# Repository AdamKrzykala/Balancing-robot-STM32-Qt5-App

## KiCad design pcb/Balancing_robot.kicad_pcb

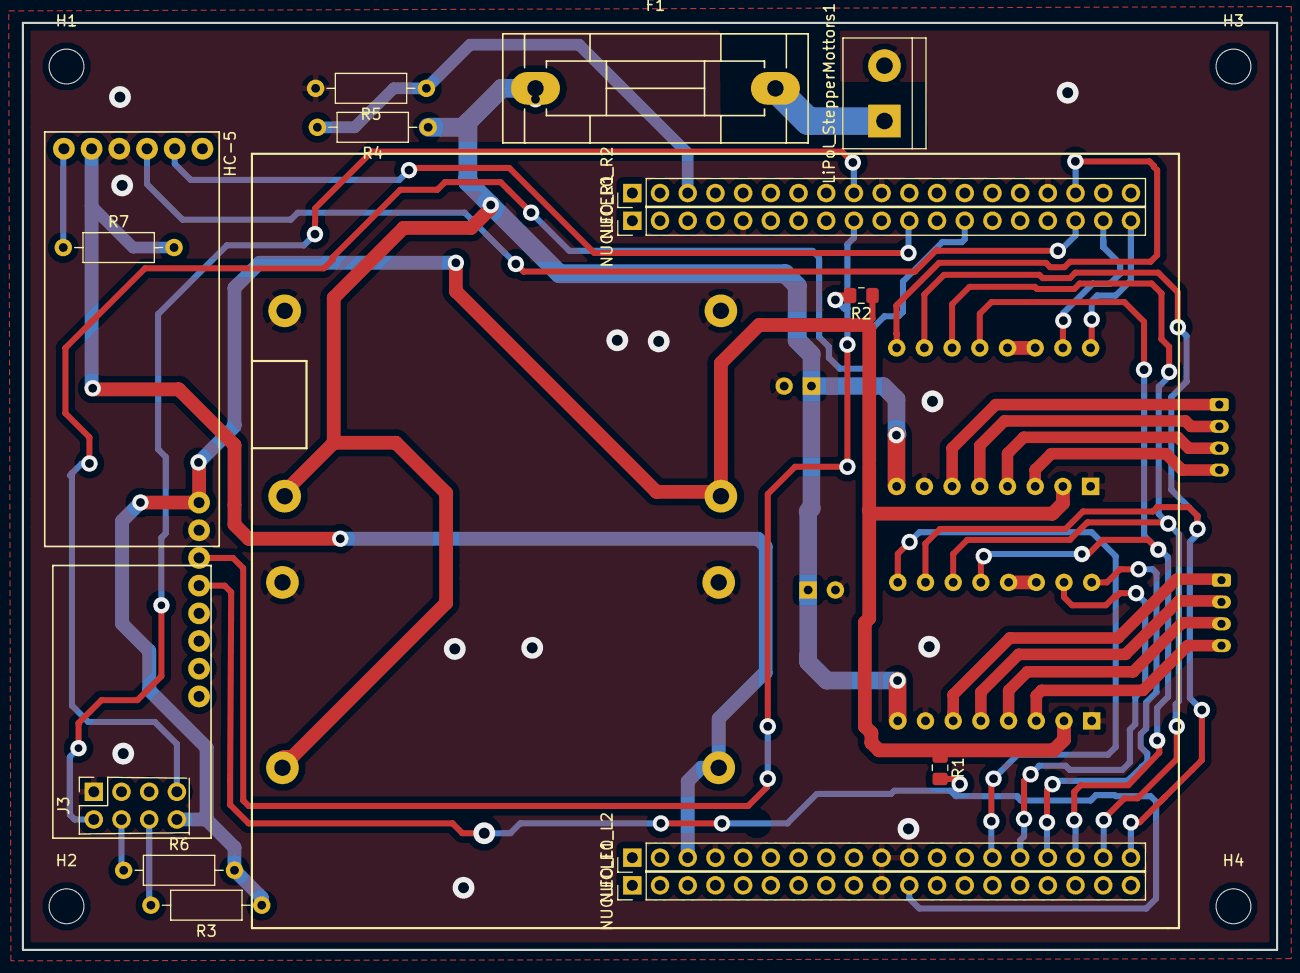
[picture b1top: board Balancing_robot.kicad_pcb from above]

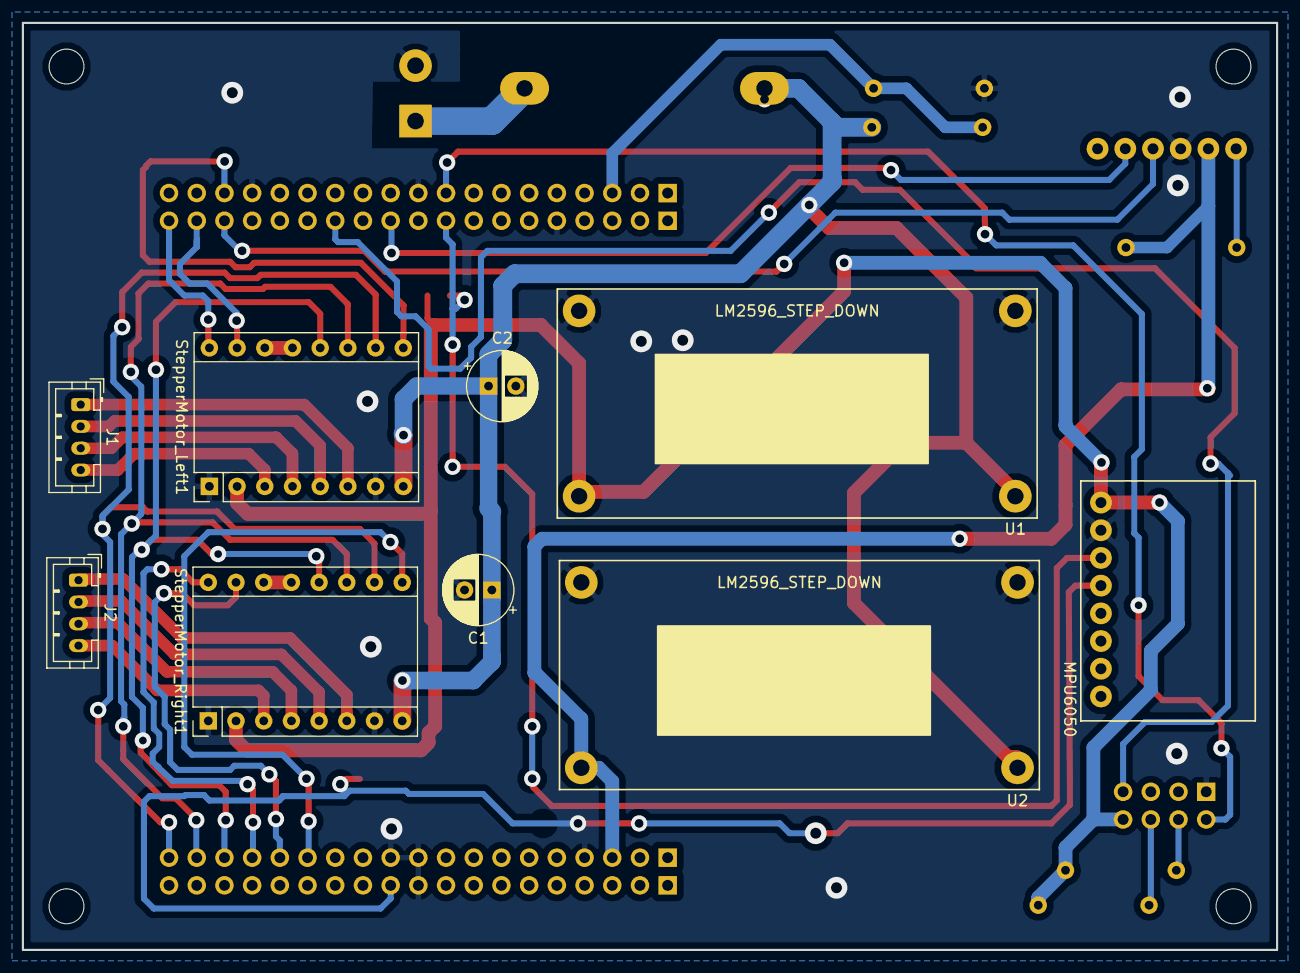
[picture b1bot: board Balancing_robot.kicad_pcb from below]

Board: 2 copper layers, 115.0 x 85.0 mm, 28 parts (9 on the bottom side), 34 nets.

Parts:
C1, C2: 47u; CP_Radial_D6.3mm_P2.50mm
F1: 4A; BEZPIECZNIK_Fuseholder5x20_horiz_SemiClosed_Casing10x25mm
H1, H2, H3, H4: MountingHole; MountingHole_3.2mm_M3
HC-5: HC05; HC-05
J1, J2: Conn_01x04_Male; JST_PH_B4B-PH-K_1x04_P2.00mm_Vertical
J3: Conn_02x04_Odd_Even; ESP8266
LiPol_StepperMottors1: Conn_01x02_Male; TerminalBlock_bornier-2_P5.08mm
MPU6050: Conn_01x08_Female; MPU6050
NUCELO_R2: Conn_01x19_Female; PinHeader_1x19_P2.54mm_Vertical
NUCLEO_L1, NUCLEO_L2: Conn_01x19_Female; PinHeader_1x19_P2.54mm_Vertical
NUCLEO_R1: Conn_01x19_Female; PinHeader_1x19_P2.54mm_Vertical
R1, R2: 3k3; R_0805_2012Metric_Pad1.15x1.40mm_HandSolder
R3, R6: 10k; R_Axial_DIN0207_L6.3mm_D2.5mm_P10.16mm_Horizontal
R4: 100k; R_Axial_DIN0207_L6.3mm_D2.5mm_P10.16mm_Horizontal
R5: 56k; R_Axial_DIN0207_L6.3mm_D2.5mm_P10.16mm_Horizontal
R7: 0R; R_Axial_DIN0207_L6.3mm_D2.5mm_P10.16mm_Horizontal
StepperMotor_Left1: Pololu_Breakout_A4988; Pololu_Breakout-16_15.2x20.3mm
StepperMotor_Right1: Pololu_Breakout_A4988; Pololu_Breakout-16_15.2x20.3mm
U1, U2: LM2596

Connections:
+3V3: J3.8, MPU6050.1, R1.1, R2.1, R3.1, R6.2, StepperMotor_Left1.2, StepperMotor_Right1.2, U1.3
+5V: HC-5.5, NUCLEO_L2.3, R7.2, U2.3
ESP_RX: J3.7, NUCLEO_R1.13
ESP_TX: J3.2, NUCELO_R2.9
GND: C1.2, C2.2, HC-5.4, J3.1, LiPol_StepperMottors1.2, MPU6050.2, NUCELO_R2.10, NUCELO_R2.16, NUCLEO_L1.10, NUCLEO_L2.4, NUCLEO_L2.10, NUCLEO_L2.11, NUCLEO_R1.5, R5.2, StepperMotor_Left1.1, StepperMotor_Left1.7, StepperMotor_Right1.1, StepperMotor_Right1.7, U1.2, U1.4, U2.2, U2.4
I2C1_SCL_MPU6050: MPU6050.3, NUCLEO_R1.9, R2.2
I2C1_SDA_MPU6050: MPU6050.4, NUCLEO_L1.11, R1.2
MS1: NUCLEO_L2.19, StepperMotor_Left1.10, StepperMotor_Right1.10
MS2: NUCLEO_L2.18, StepperMotor_Left1.11, StepperMotor_Right1.11
MS3: NUCLEO_L2.17, StepperMotor_Left1.12, StepperMotor_Right1.12
unnamed: F1.2, LiPol_StepperMottors1.1
unnamed: HC-5.6, R7.1
unnamed: J1.1, StepperMotor_Left1.6
unnamed: J1.2, StepperMotor_Left1.5
unnamed: J1.3, StepperMotor_Left1.4
unnamed: J1.4, StepperMotor_Left1.3
unnamed: J2.1, StepperMotor_Right1.6
unnamed: J2.2, StepperMotor_Right1.5
unnamed: J2.3, StepperMotor_Right1.4
unnamed: J2.4, StepperMotor_Right1.3
unnamed: J3.4, R6.1
unnamed: StepperMotor_Left1.13, StepperMotor_Left1.14
unnamed: StepperMotor_Right1.13, StepperMotor_Right1.14
RST: J3.6, R3.2
SD_DIR1: NUCLEO_R1.19, StepperMotor_Left1.16
SD_DIR2: NUCLEO_L2.16, StepperMotor_Right1.16
SD_EN1: NUCELO_R2.17, StepperMotor_Left1.9
SD_EN2: NUCLEO_L2.14, StepperMotor_Right1.9
SD_STEP1: NUCLEO_R1.18, StepperMotor_Left1.15
SD_STEP2: NUCLEO_L2.15, StepperMotor_Right1.15
USART1_RX_HC05: HC-5.3, NUCLEO_R1.17
USART1_TX_HC05: HC-5.2, NUCLEO_R1.11
VBAT_ADC: NUCELO_R2.3, R4.2, R5.1
VMOT: C1.1, C2.1, F1.1, R4.1, StepperMotor_Left1.8, StepperMotor_Right1.8, U1.1, U2.1

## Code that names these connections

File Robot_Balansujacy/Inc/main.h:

/* USER CODE BEGIN Header */
/**
  ******************************************************************************
  * @file           : main.h
  * @brief          : Header for main.c file.
  *                   This file contains the common defines of the application.
  ******************************************************************************
  * @attention
  *
  * <h2><center>&copy; Copyright (c) 2019 STMicroelectronics.
  * All rights reserved.</center></h2>
  *
  * This software component is licensed by ST under Ultimate Liberty license
  * SLA0044, the "License"; You may not use this file except in compliance with
  * the License. You may obtain a copy of the License at:
  *                             www.st.com/SLA0044
  *
  ******************************************************************************
  */
/* USER CODE END Header */

/* Define to prevent recursive inclusion -------------------------------------*/
#ifndef __MAIN_H
#define __MAIN_H

#ifdef __cplusplus
extern "C" {
#endif

/* Includes ------------------------------------------------------------------*/
#include "stm32f1xx_hal.h"

/* Private includes ----------------------------------------------------------*/
/* USER CODE BEGIN Includes */

/* USER CODE END Includes */

/* Exported types ------------------------------------------------------------*/
/* USER CODE BEGIN ET */

/* USER CODE END ET */

/* Exported constants --------------------------------------------------------*/
/* USER CODE BEGIN EC */

/* USER CODE END EC */

/* Exported macro ------------------------------------------------------------*/
/* USER CODE BEGIN EM */

/* USER CODE END EM */

/* Exported functions prototypes ---------------------------------------------*/
void Error_Handler(void);

/* USER CODE BEGIN EFP */

/* USER CODE END EFP */

/* Private defines -----------------------------------------------------------*/
#define TIM3_PERIOD 799
#define TIM3_PRESCALER 9999
#define B1_Pin GPIO_PIN_13
#define B1_GPIO_Port GPIOC
#define B1_EXTI_IRQn EXTI15_10_IRQn
#define MS1_Pin GPIO_PIN_0
#define MS1_GPIO_Port GPIOC
#define MS2_Pin GPIO_PIN_1
#define MS2_GPIO_Port GPIOC
#define SD_EN2_Pin GPIO_PIN_0
#define SD_EN2_GPIO_Port GPIOA
#define SD_STEP2_Pin GPIO_PIN_1
#define SD_STEP2_GPIO_Port GPIOA
#define SD_DIR2_Pin GPIO_PIN_4
#define SD_DIR2_GPIO_Port GPIOA
#define LD2_Pin GPIO_PIN_5
#define LD2_GPIO_Port GPIOA
#define SD_EN1_Pin GPIO_PIN_4
#define SD_EN1_GPIO_Port GPIOC
#define ADC1_IN15_LiPol_Pin GPIO_PIN_5
#define ADC1_IN15_LiPol_GPIO_Port GPIOC
#define MS3_Pin GPIO_PIN_0
#define MS3_GPIO_Port GPIOB
#define SD_DIR1_Pin GPIO_PIN_8
#define SD_DIR1_GPIO_Port GPIOA
#define USART_TX_HC05_Pin GPIO_PIN_9
#define USART_TX_HC05_GPIO_Port GPIOA
#define USART1_RX_HC05_Pin GPIO_PIN_10
#define USART1_RX_HC05_GPIO_Port GPIOA
#define TMS_Pin GPIO_PIN_13
#define TMS_GPIO_Port GPIOA
#define TCK_Pin GPIO_PIN_14
#define TCK_GPIO_Port GPIOA
#define SWO_Pin GPIO_PIN_3
#define SWO_GPIO_Port GPIOB
#define SD_STEP1_Pin GPIO_PIN_4
#define SD_STEP1_GPIO_Port GPIOB
#define I2C1_SCL_MPU6050_Pin GPIO_PIN_6
#define I2C1_SCL_MPU6050_GPIO_Port GPIOB
#define I2C1_SDA_MPU6050_Pin GPIO_PIN_7
#define I2C1_SDA_MPU6050_GPIO_Port GPIOB
/* USER CODE BEGIN Private defines */

/* USER CODE END Private defines */

#ifdef __cplusplus
}
#endif

#endif /* __MAIN_H */

/************************ (C) COPYRIGHT STMicroelectronics *****END OF FILE****/

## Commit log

2019-06-19 Wygenerowanie pustego projektu z systemem FreeRTOS
2019-06-20 Skonfigurowanie tim3
2019-06-20 Uzycie DWT do pomiaru mikrosekund
2019-06-20 Utworzenie watku mierzacego napiecie na LiPolu
2019-06-21 Implementacja PID, Roll i plynnego sterowania A4988
2019-06-22 Poprawa w wyliczaniu wartosci RPM
2019-06-22 Calkowite wylaczenie silnikow przy napieciu poniezej 11V
2019-06-22 Dioda ostrzegawcza przy napieciu ponizej 11V i calkowite wylaczenie silnikow ponizej 10.5V
2019-06-25 Utworzenie pustego projektu aplikacji do wizualziacj
2019-06-25 Uruchomienie bibliotek qcustomplot
2019-06-26 Rozpoczecie pracy nad klasa do obslugi komunikacji Bluetooth
2019-06-26 Rozpoczecie pracy nad obsluga komunikacji
2019-06-27 Wstepny szablon komunikacji i rozpoczecie prac nad interfejsem
2019-06-30 Wyswietlanie stanu LiPo
2019-07-01 Dodanie wizualizacji rotacji w OpenGL
2019-07-02 Stworzenie okna do komunikacji z urzadzeniem
2019-07-07 Rozpoczecie pracy nad panelem operatorskim
2019-07-08 Aplikacja odbiera pojedynczy bajt z robota
2019-07-09 Odbieranie nastaw PID
2019-07-09 Wysylanie nastwa PID
2019-07-10 Wstepna wersja transmisji dwukierunkowej
2019-07-12 ROzpoczecie proby przerobienia na sterowanie PWM
2019-07-29 Przesylanie predkosci przod-tyl do robota
2019-07-30 Rezygnacja z FreeRTOS. Przerobienie sterowania silnikami na PWM
2019-08-01 Zapisywanie ustawien
2019-08-16 Polaczenie FreeRTOS i PWM
2019-08-17 Calkowite przerobienie projektu na wykorzystanie FreeRTOS
2019-08-21 Jazda p/t/p/l na freertos
2019-08-28 Kompensacja kata wychylenia magnetometru
2019-08-30 Implementacja filtru kalmana - pitch
2019-09-01 Obsluga przycisku anuluj w oknie komunikacji
2019-09-01 Dodanie dodatkowych ikon w oknie glownym
2019-09-02 Obsluga przycisku "zakoncz"
2019-09-03 Dodanie ikonki bluetooth
2019-09-04 Naprawa bledu wyswietlania figury w oknie OpenGL
2019-09-04 Dodanie wykresow dla filtru Kalmana
2019-09-05 Odrzucanie wyszukanych ponownie tych samych urzadzen
2019-09-05 Dodanie przycisku start/stop dla wykresow
2019-09-07 Dodanie przycisku do resetowania splittera
2019-09-12 Poprawa wyliczania kata Yaw wzgledem orientacji osi Z
2019-09-12 Optymalizacja odbierania danych oraz dodanie przycisku do resetowania wykresow
2019-09-13 Dzialajacy filtr Kalmana dla rotacji w trzech osiach
2019-09-14 Odbieranie i wyswietlanie RPY z filtru Kalmana
2019-09-14 Wysylanie RPY dla filtru Kalmana
2019-09-14 Mozliwosc wyboru filtra bioracego udzial w algorytmie sterowania
2019-09-14 Mozliwosc wyboru wartosci wariancji szumu procesowego
2019-09-14 Odbieranie dodatkowych zmiennych: wariancja oraz ktory filtr
2019-09-16 Implementacja filtru Madgwick'a
2019-09-16 Wysylanie RPY z filtru Magdwicka
2019-09-16 Odbieranie RPY z filtru Magdwicka
2019-09-16 Odbieranie parametru beta
2019-09-16 Wysylanie parametru beta
2019-09-17 Automatyczne rozlaczenie po przekroczeniu limitu czasu zadania
2019-09-18 Naprawa orientacji obiektu w openGL
2019-09-20 Optymalizacja pomiaru napiecia LiPol
2019-09-21 Dodanie komunikatu o niskim stanie baterii
2019-09-24 Niski stan baterii wyswietla komunikat ale nie zamyka aplikacji
2019-09-24 Uruchomienie pustego szablonu pracy dyplomowej (Kubik)
2019-09-25 Przygotowanie wstepnej wersji spisu tresci
2019-09-28 Poprawki w numeracji rozdzialow
2019-09-28 Naprawa bledu zwiazanego z odbieraniem niepoprawnej ramki
2019-10-06 Wygenerowanie projektu
2019-10-06 Pojedyncze wysylanie danych dla filtru
2019-10-06 Wyswietlanie danych z jednego filtru na raz
2019-10-16 Ukonczony model dynamiki i regulatory PID
2019-11-03 Kompensacja efektu Soft Iron
2019-11-03 Usprawnienie wyliczania rpy dla zyroskopu
2019-11-05 Wstepne wersje. Rozdzial 2 i 3
2019-11-05 Wstepne wersje rozdzialu 2 i 3
2019-11-11 Poprawki w rozdziale 02 oraz wstepne wersje rozdzialu 03 i 04
2019-11-19 Poprawki w rozdziale 03 i 04 oraz rozpoczecie pracy nad rozdzialem 05
2019-11-19 Poprawki w rozdziale 05
2019-11-20 Wstepna wersja rozdzialu 05
2019-11-22 Wstepna wersja rozdzialu 06
2019-12-14 Wersja finalowa
2021-03-02 Files managment
